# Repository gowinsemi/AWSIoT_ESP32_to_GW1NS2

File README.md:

# AWS IoT - GW1NS2 to ESP32 Example

## Project Information

This project provides a basic example of how to connect the Gowin DK-START-GW1NS2 Development Board to AWS IoT via ESP32 WiFi Module.  Demo lights up one of 4 LEDs on each DK-START-GW1NS2 board connected to the cloud.  Push button "KEY1" can be pressed on any of the DK-START boards to change the LED that is on for all boards.

- The ESP32 program requests information to connect to a WiFi network and to the AWS IoT MQTT broker via UART.
- The Cortex M3 on the GW1NS2 SoC FPGA responds to the information requests appropriately.

​			Note - the voltage translator in the above picture is no longer required.*

### Install GNU MCU Eclipse

1. Obtain Gowin's GNU MCU Eclipse software package
   1. Extract `eclipse_tools > installer > jdk*.exe` to install Java SE Development Kit (use default settings)
   2. Test installation by opening command line and entering `java -version`
   3. `eclipse_tools > installer > Setup_JLink*.exe` to install debugger (use defaults)
2. Open Eclipse and set up project for Cortex M3
   1. Go to properties for the  `eclipse_tools_*` folder and uncheck `Read-only`
   2. Open `*\eclipse_tools_*\eclipse_tools_*\eclipse_tools\eclipse\eclipse.exe`
   3. Follow RN519 - MCU IDE Reference Manual for the rest of the instructions

### Software Installation Instructions for Arduino IDE and ESP32:

1. https://www.arduino.cc/en/Main/Software
2. `File > Preferences > Additional Board Manager URLs` and add `https://dl.espressif.com/dl/package_esp32_index.json`
3. `Tools > Board > Boards Manager… > ESP32 by Espressif Systems`
4. `Tools > Board > ESP32 Dev Module`
5. You can test setup by:
   1. Plugging in board > `Examples > WiFi > WiFiScan`
   2. `Tools > Port > Select COM port for board`
   3. `Tools > Serial Monitor > Select 115200 Baud`
   4. Upload on Arduino IDE > IDE should connect to board > Durring "Connecting..." you may have to press boot button.
   5. After code loads you should see WiFi networks availible in COM port.

## Firmware Setup and Loading

### Replace SSID and AWS Credentials

1. Open`\trunk\GW1NS2\uart2esp32\USER\main.c`

2. Replace the following lines with your SSID and AWS IoT credentials

   *const char SSID[]	=	"iPhone\n";*
   *const char PW[]		=	"iphone123\n";*
   *const char URL[]	=	"a2pb2f9st3ros6-ats.iot.us-east-2.amazonaws.com\n";*
   *const char THING[]	=	"ESP32\n";*
   *const char ROOTCA[]	=	"-----BEGIN CERTIFICATE-----\n\*
   *------------------------------------------------------------------------------------------------------------------\n\*
   *....*
   *-----END CERTIFICATE-----\r";*

   *const char DEVICECERT[]	=	"-----BEGIN CERTIFICATE-----\n\*
   *------------------------------------------------------------------------------------------------------------------\n\*
   *....*
   *-----END CERTIFICATE-----\r";*

   *const char DEVICEKEY []	=	"-----BEGIN RSA PRIVATE KEY-----\n\*
   *------------------------------------------------------------------------------------------------------------------\n\*
   *....*
   *-----END RSA PRIVATE KEY-----\r";*

3. Import uart2esp32 project --> Clean -- > Build

4. GW1NS2C firmware file will be uart.bin in the Debug folder

### Load GW1NS2C firmware files

1. FPGA --> `.\trunk\Firmware\GW1NS2_FPGA.fs` 
   1. Program in Gowin Programmer.  Choose Embedded Flash Mode
2. MCU --> `.\trunk\GW1NS2\uart2esp32\Debug\uart.bin`

### Load ESP32

1. Open `.\trunk\AWS_IOT\examples\pubSubTest\pubSubTest.ino` in Arduino IDE
2. Compile and Upload
   1. Note: press "Boot" push button on ESP32 while IDE says "Connecting..."
   2. Note: UART wires between ESP32 and GW1NS2C boards must be removed for ESP32 loading

## Connecting GW1NS2C DK-START and ESP32 Boards Together

## Running the Demo

1. With both boards connected to each other and powered press the `EN` reset button on the ESP32 and the `RSET` on the GW1NS2C board.  Release the GW1NS2C reset first, followed by the ESP32 reset a second or more later.
2. You can monitor the status of the demo platform connecting to AWS through the ESP32 serial port using a terminal program like Realterm.
3. After the device is connected press `KEY1`.  A number from 1-4 will be incremented and sent to the cloud.  All connected devices including the device that had the key pressed will receive the new number from the broker.  The new LED will light corresponding to the number 1-4 received.

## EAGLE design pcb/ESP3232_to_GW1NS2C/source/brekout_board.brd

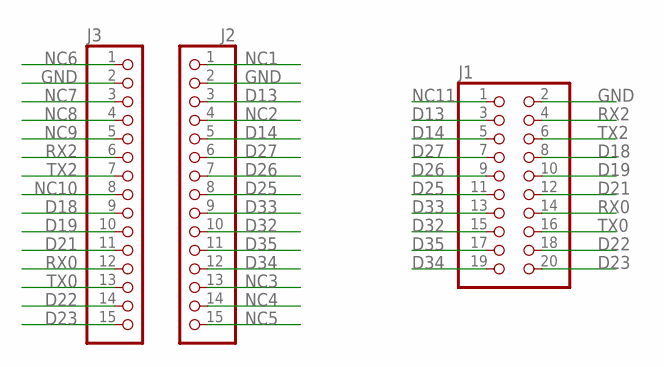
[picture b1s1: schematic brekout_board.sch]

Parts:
J1: PINHD-2X10; 2X10
J2, J3: PINHD-1X15; 1X15

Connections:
D13: J1.3, J2.3
D14: J1.5, J2.5
D18: J1.8, J3.9
D19: J1.10, J3.10
D21: J1.12, J3.11
D22: J1.18, J3.14
D23: J1.20, J3.15
D25: J1.11, J2.8
D26: J1.9, J2.7
D27: J1.7, J2.6
D32: J1.15, J2.10
D33: J1.13, J2.9
D34: J1.19, J2.12
D35: J1.17, J2.11
GND: J1.2, J2.2, J3.2
NC1: J2.1
NC2: J2.4
NC3: J2.13
NC4: J2.14
NC5: J2.15
NC6: J3.1
NC7: J3.3
NC8: J3.4
NC9: J3.5
NC10: J3.8
NC11: J1.1
RX0: J1.14, J3.12
RX2: J1.4, J3.6
TX0: J1.16, J3.13
TX2: J1.6, J3.7

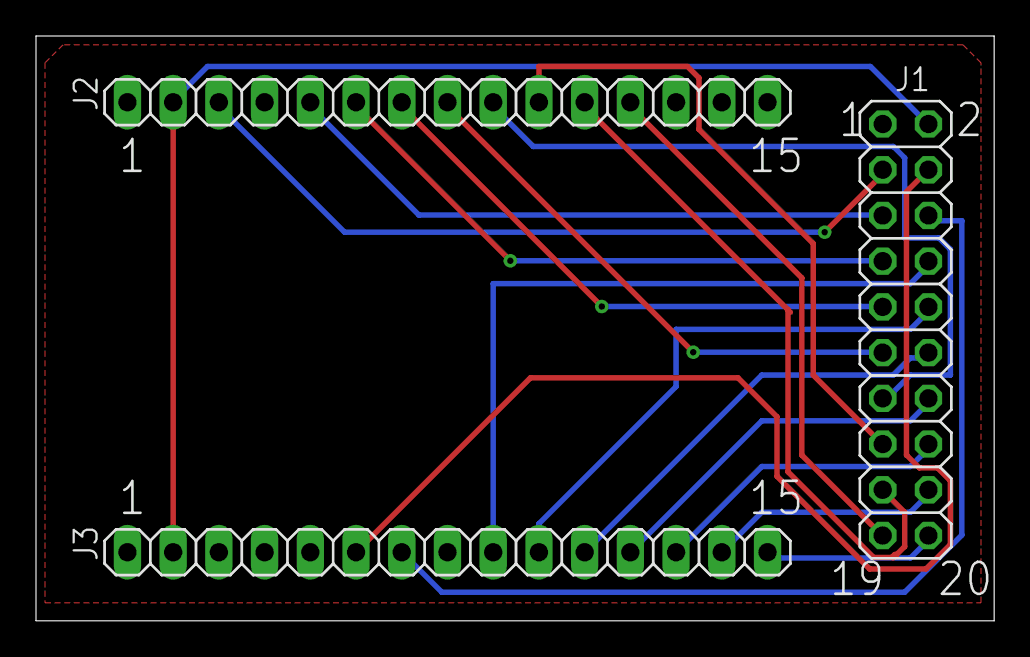
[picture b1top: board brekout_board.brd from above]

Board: 2 copper layers, 53.2 x 32.5 mm, 3 parts (0 on the bottom side), 19 nets.

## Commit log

2019-03-04 readme.md and initial check in
2019-03-04 all user entries through uart except for certificates
2019-03-05 added function to use uart entries for certs
2019-03-05 added ability to enter login credentials via uart
2019-03-05 updated readme docs
2019-03-06 Adding GW1NS2 Cortex M3 Project
2019-03-06 updated GW1NS2/readme.md
2019-03-06 Updated AWS IoT Readme.md
2019-03-06 updated main project README.md
2019-03-07 adding fpga design
2019-03-20 connected ESP32 and GW1NS2 board together
2019-03-20 updated docs, notes and constants
2019-03-20 gw1ns readme pulled into main readme.md
2019-03-26 push button issue between multiple boards resolved
2019-03-28 Adding esp32 to GW1NS2C Start Board Adapter
2019-04-10 2 layer PCB update
2019-04-25 certs
2019-04-25 m3 program batch file loader
2019-04-25 updated pinout due to silicon failures
2019-04-25 working demo check in.
2019-04-29 credentials update
2019-04-29 replacing with working fpga design
2019-04-29 adding provision loading tools.
2019-04-29 credential update
2019-04-29 bitstream update
2019-10-11 BKP_3 and BKP_4 credentials
